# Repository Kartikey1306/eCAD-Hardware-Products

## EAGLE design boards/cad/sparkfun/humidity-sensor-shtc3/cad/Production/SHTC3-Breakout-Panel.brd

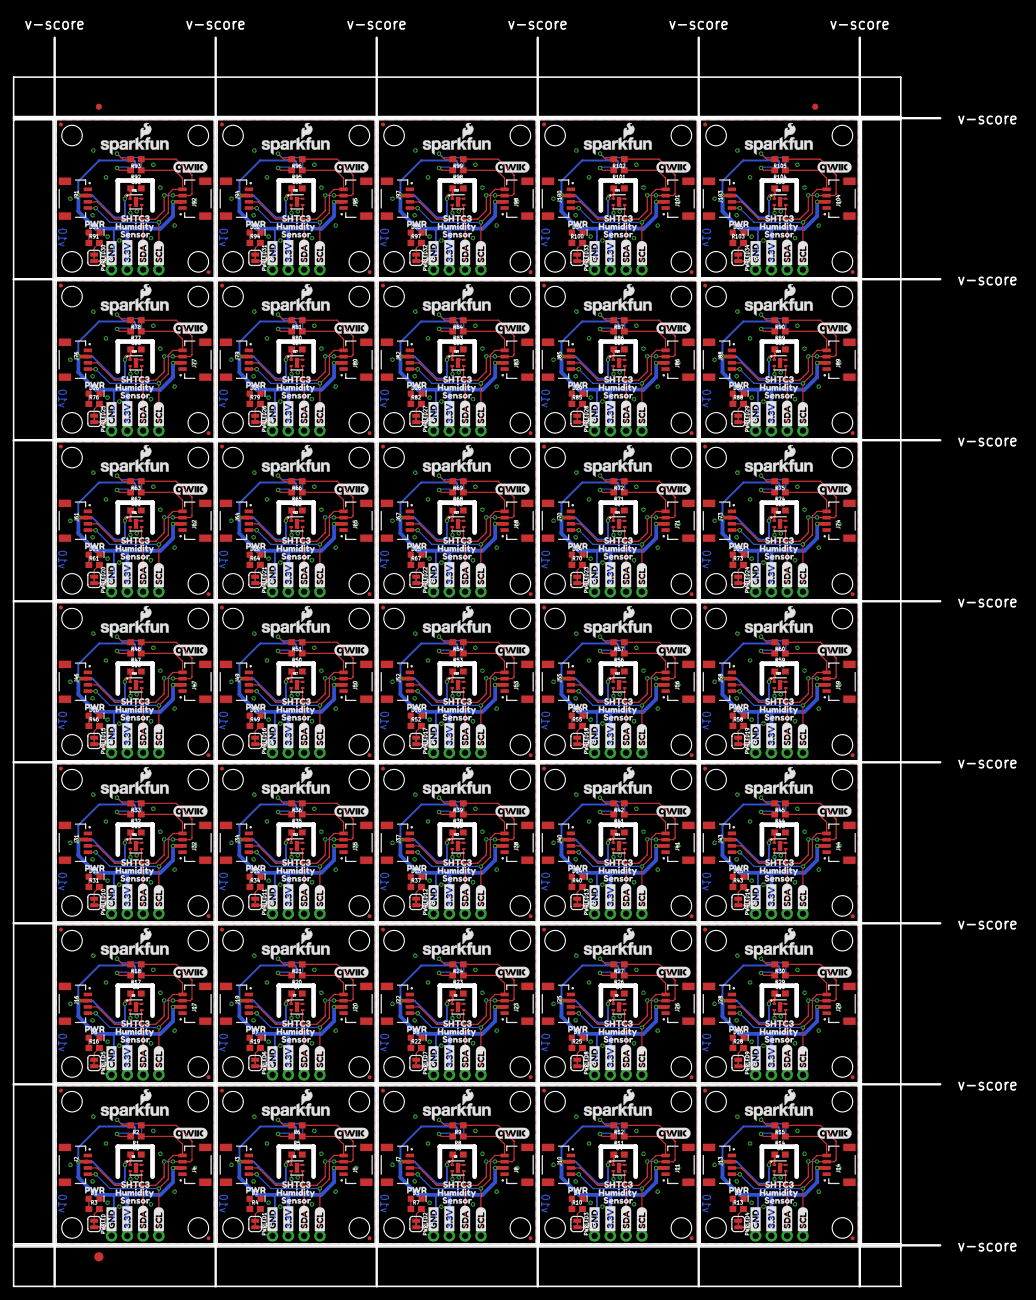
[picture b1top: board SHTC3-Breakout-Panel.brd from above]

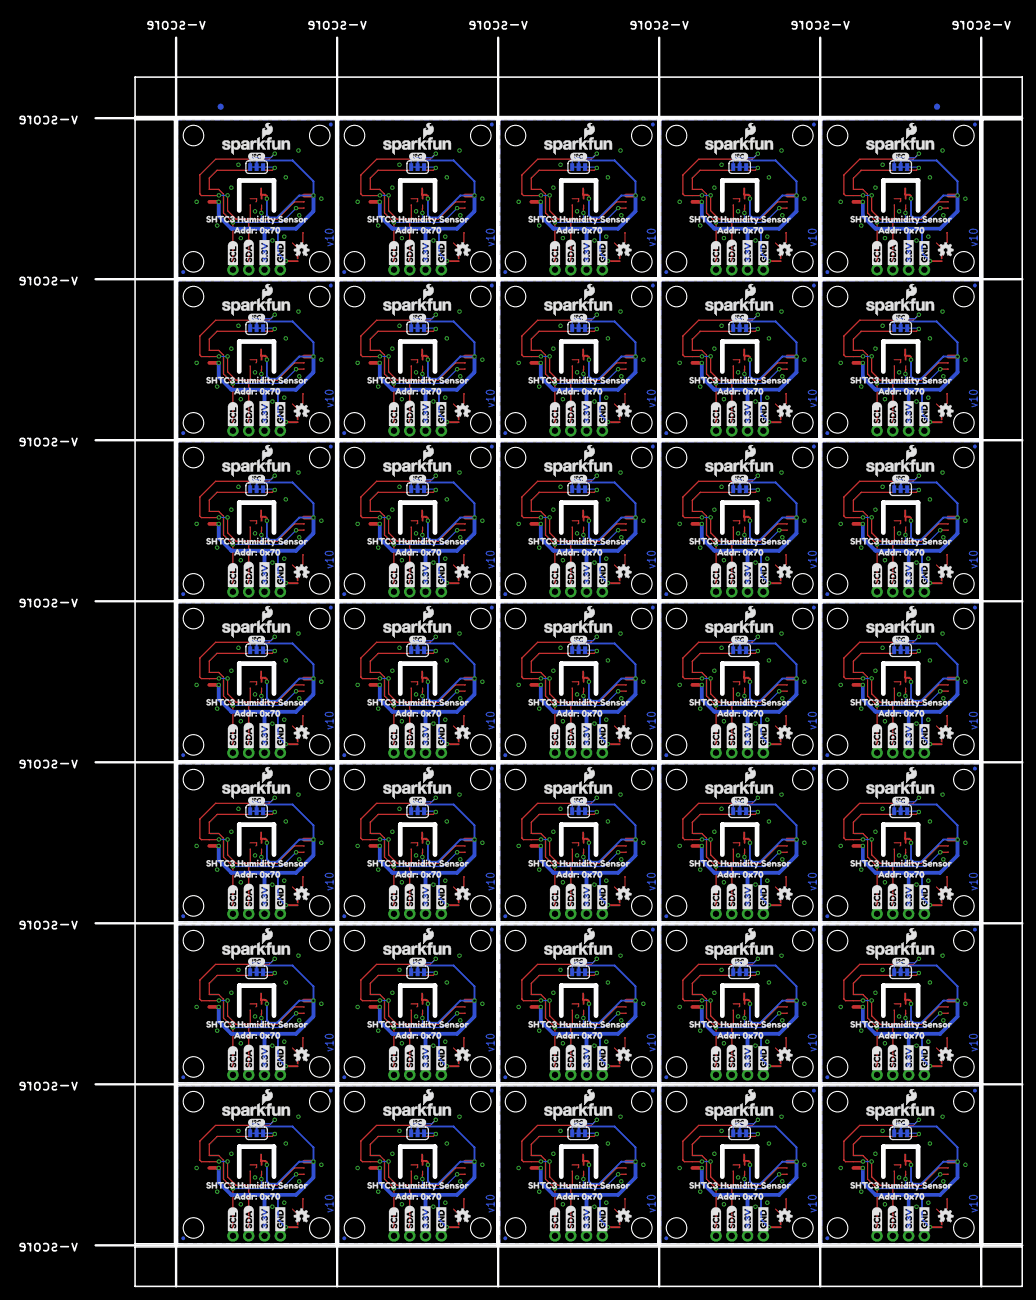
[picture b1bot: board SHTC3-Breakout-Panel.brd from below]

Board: 2 copper layers, 149.1 x 200.9 mm, 1370 parts (422 on the bottom side), 280 nets.

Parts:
C1, C2, C3, C4, C5, C6, C7, C8, C9, C10, C11, C12, C13, C14, C15, C16, C17, C18, C19, C20, C21, C22, C23, C24, C25, C26, C27, C28, C29, C30, C31, C32, C33, C34, C35: 0.1uF; 0603
D1, D2, D3, D4, D5, D6, D7, D8, D9, D10, D11, D12, D13, D14, D15, D16, D17, D18, D19, D20, D21, D22, D23, D24, D25, D26, D27, D28, D29, D30, D31, D32, D33, D34, D35: RED; LED-0603
E$1, E$2, E$3, E$4: FIDUCIAL-1X2
E$5: FIDUCIAL-1.5X3
I2C, I2C1, I2C2, I2C3, I2C4, I2C5, I2C6, I2C7, I2C8, I2C9, I2C10, I2C11, I2C12, I2C13, I2C14, I2C15, I2C16, I2C17, I2C18, I2C19, I2C20, I2C21, I2C22, I2C23, I2C24, I2C25, I2C26, I2C27, I2C28, I2C29, I2C30, I2C31, I2C32, I2C33, I2C34: JUMPER-SMT_3_2-NC_TRACE_SILK; SMT-JUMPER_3_2-NC_TRACE_SILK
J1, J6, J9, J12, J15, J18, J21, J24, J27, J30, J33, J36, J39, J42, J45, J48, J51, J54, J57, J60, J63, J66, J69, J72, J75, J78, J81, J84, J87, J90, J93, J96, J99, J102, J105: 1X04_NO_SILK
J2, J3, J4, J5, J7, J8, J10, J11, J13, J14, J16, J17, J19, J20, J22, J23, J25, J26, J28, J29, J31, J32, J34, J35, J37, J38, J40, J41, J43, J44, J46, J47, J49, J50, J52, J53, J55, J56, J58, J59, J61, J62, J64, J65, J67, J68, J70, J71, J73, J74, J76, J77, J79, J80, J82, J83, J85, J86, J88, J89, J91, J92, J94, J95, J97, J98, J100, J101, J103, J104: QWIIC_RIGHT_ANGLE; JST04_1MM_RA
JP1, JP2, JP5, JP6, JP11, JP12, JP13, JP14, JP19, JP20, JP21, JP22, JP27, JP28, JP29, JP30, JP35, JP36, JP37, JP38, JP43, JP44, JP45, JP46, JP51, JP52, JP53, JP54, JP59, JP60, JP61, JP62, JP67, JP68, JP69, JP70, JP75, JP76, JP77, JP78, JP83, JP84, JP85, JP86, JP91, JP92, JP93, JP94, JP99, JP100, JP101, JP102, JP107, JP108, JP109, JP110, JP115, JP116, JP117, JP118, JP123, JP124, JP125, JP126, JP131, JP132, JP133, JP134, JP139, JP140, JP141, JP142, JP147, JP148, JP149, JP150, JP155, JP156, JP157, JP158, JP163, JP164, JP165, JP166, JP171, JP172, JP173, JP174, JP179, JP180, JP181, JP182, JP187, JP188, JP189, JP190, JP195, JP196, JP197, JP198, JP203, JP204, JP205, JP206, JP211, JP212, JP213, JP214, JP219, JP220, JP221, JP222, JP227, JP228, JP229, JP230, JP235, JP236, JP237, JP238, JP243, JP244, JP245, JP246, JP251, JP252, JP253, JP254, JP259, JP260, JP261, JP262, JP267, JP268, JP269, JP270, JP275, JP276, JP277, JP278: FIDUCIALUFIDUCIAL; MICRO-FIDUCIAL
JP3, JP4, JP7, JP8, JP9, JP10, JP15, JP16, JP17, JP18, JP23, JP24, JP25, JP26, JP31, JP32, JP33, JP34, JP39, JP40, JP41, JP42, JP47, JP48, JP49, JP50, JP55, JP56, JP57, JP58, JP63, JP64, JP65, JP66, JP71, JP72, JP73, JP74, JP79, JP80, JP81, JP82, JP87, JP88, JP89, JP90, JP95, JP96, JP97, JP98, JP103, JP104, JP105, JP106, JP111, JP112, JP113, JP114, JP119, JP120, JP121, JP122, JP127, JP128, JP129, JP130, JP135, JP136, JP137, JP138, JP143, JP144, JP145, JP146, JP151, JP152, JP153, JP154, JP159, JP160, JP161, JP162, JP167, JP168, JP169, JP170, JP175, JP176, JP177, JP178, JP183, JP184, JP185, JP186, JP191, JP192, JP193, JP194, JP199, JP200, JP201, JP202, JP207, JP208, JP209, JP210, JP215, JP216, JP217, JP218, JP223, JP224, JP225, JP226, JP231, JP232, JP233, JP234, JP239, JP240, JP241, JP242, JP247, JP248, JP249, JP250, JP255, JP256, JP257, JP258, JP263, JP264, JP265, JP266, JP271, JP272, JP273, JP274, JP279, JP280: STAND-OFF
LOGO1, LOGO5, LOGO9, LOGO13, LOGO17, LOGO21, LOGO25, LOGO29, LOGO33, LOGO37, LOGO41, LOGO45, LOGO49, LOGO53, LOGO57, LOGO61, LOGO65, LOGO69, LOGO73, LOGO77, LOGO81, LOGO85, LOGO89, LOGO93, LOGO97, LOGO101, LOGO105, LOGO109, LOGO113, LOGO117, LOGO121, LOGO125, LOGO129, LOGO133, LOGO137: OSHW-LOGOMINI; OSHW-LOGO-MINI
LOGO2, LOGO3, LOGO6, LOGO7, LOGO10, LOGO11, LOGO14, LOGO15, LOGO18, LOGO19, LOGO22, LOGO23, LOGO26, LOGO27, LOGO30, LOGO31, LOGO34, LOGO35, LOGO38, LOGO39, LOGO42, LOGO43, LOGO46, LOGO47, LOGO50, LOGO51, LOGO54, LOGO55, LOGO58, LOGO59, LOGO62, LOGO63, LOGO66, LOGO67, LOGO70, LOGO71, LOGO74, LOGO75, LOGO78, LOGO79, LOGO82, LOGO83, LOGO86, LOGO87, LOGO90, LOGO91, LOGO94, LOGO95, LOGO98, LOGO99, LOGO102, LOGO103, LOGO106, LOGO107, LOGO110, LOGO111, LOGO114, LOGO115, LOGO118, LOGO119, LOGO122, LOGO123, LOGO126, LOGO127, LOGO130, LOGO131, LOGO134, LOGO135, LOGO138, LOGO139: SFE_LOGO_NAME_FLAME.1_INCH; SFE_LOGO_NAME_FLAME_.1
LOGO4, LOGO8, LOGO12, LOGO16, LOGO20, LOGO24, LOGO28, LOGO32, LOGO36, LOGO40, LOGO44, LOGO48, LOGO52, LOGO56, LOGO60, LOGO64, LOGO68, LOGO72, LOGO76, LOGO80, LOGO84, LOGO88, LOGO92, LOGO96, LOGO100, LOGO104, LOGO108, LOGO112, LOGO116, LOGO120, LOGO124, LOGO128, LOGO132, LOGO136, LOGO140: REVISION
PWRLED, PWRLED1, PWRLED2, PWRLED3, PWRLED4, PWRLED5, PWRLED6, PWRLED7, PWRLED8, PWRLED9, PWRLED10, PWRLED11, PWRLED12, PWRLED13, PWRLED14, PWRLED15, PWRLED16, PWRLED17, PWRLED18, PWRLED19, PWRLED20, PWRLED21, PWRLED22, PWRLED23, PWRLED24, PWRLED25, PWRLED26, PWRLED27, PWRLED28, PWRLED29, PWRLED30, PWRLED31, PWRLED32, PWRLED33, PWRLED34: JUMPER-SMT_2_NC_TRACE_SILK; SMT-JUMPER_2_NC_TRACE_SILK
R1, R2, R5, R6, R8, R9, R11, R12, R14, R15, R17, R18, R20, R21, R23, R24, R26, R27, R29, R30, R32, R33, R35, R36, R38, R39, R41, R42, R44, R45, R47, R48, R50, R51, R53, R54, R56, R57, R59, R60, R62, R63, R65, R66, R68, R69, R71, R72, R74, R75, R77, R78, R80, R81, R83, R84, R86, R87, R89, R90, R92, R93, R95, R96, R98, R99, R101, R102, R104, R105: 2.2k; 0603
R3, R4, R7, R10, R13, R16, R19, R22, R25, R28, R31, R34, R37, R40, R43, R46, R49, R52, R55, R58, R61, R64, R67, R70, R73, R76, R79, R82, R85, R88, R91, R94, R97, R100, R103: 1k; 0603
U1, U2, U3, U4, U5, U6, U7, U8, U9, U10, U11, U12, U13, U14, U15, U16, U17, U18, U19, U20, U21, U22, U23, U24, U25, U26, U27, U28, U29, U30, U31, U32, U33, U34, U35: SHTC3
U$1, U$25, U$43, U$59, U$75, U$91, U$107, U$123, U$139, U$155, U$171, U$187, U$203, U$219, U$235, U$251, U$267, U$283, U$299, U$315, U$331, U$347, U$363, U$379, U$395, U$411, U$427, U$443, U$459, U$475, U$491, U$507, U$523, U$539, U$555: ADDR#_0X700
U$2, U$28, U$44, U$60, U$76, U$92, U$108, U$124, U$140, U$156, U$172, U$188, U$204, U$220, U$236, U$252, U$268, U$284, U$300, U$316, U$332, U$348, U$364, U$380, U$396, U$412, U$428, U$444, U$460, U$476, U$492, U$508, U$524, U$540, U$556: PWR_TO
U$3, U$14, U$17, U$22, U$34, U$37, U$50, U$53, U$66, U$69, U$82, U$85, U$98, U$101, U$114, U$117, U$130, U$133, U$146, U$149, U$162, U$165, U$178, U$181, U$194, U$197, U$210, U$213, U$226, U$229, U$242, U$245, U$258, U$261, U$274, U$277, U$290, U$293, U$306, U$309, U$322, U$325, U$338, U$341, U$354, U$357, U$370, U$373, U$386, U$389, U$402, U$405, U$418, U$421, U$434, U$437, U$450, U$453, U$466, U$469, U$482, U$485, U$498, U$501, U$514, U$517, U$530, U$533, U$546, U$549: GND1
U$4, U$13, U$18, U$21, U$33, U$38, U$49, U$54, U$65, U$70, U$81, U$86, U$97, U$102, U$113, U$118, U$129, U$134, U$145, U$150, U$161, U$166, U$177, U$182, U$193, U$198, U$209, U$214, U$225, U$230, U$241, U$246, U$257, U$262, U$273, U$278, U$289, U$294, U$305, U$310, U$321, U$326, U$337, U$342, U$353, U$358, U$369, U$374, U$385, U$390, U$401, U$406, U$417, U$422, U$433, U$438, U$449, U$454, U$465, U$470, U$481, U$486, U$497, U$502, U$513, U$518, U$529, U$534, U$545, U$550: 3#3V2
U$5, U$16, U$19, U$27, U$36, U$39, U$52, U$55, U$68, U$71, U$84, U$87, U$100, U$103, U$116, U$119, U$132, U$135, U$148, U$151, U$164, U$167, U$180, U$183, U$196, U$199, U$212, U$215, U$228, U$231, U$244, U$247, U$260, U$263, U$276, U$279, U$292, U$295, U$308, U$311, U$324, U$327, U$340, U$343, U$356, U$359, U$372, U$375, U$388, U$391, U$404, U$407, U$420, U$423, U$436, U$439, U$452, U$455, U$468, U$471, U$484, U$487, U$500, U$503, U$516, U$519, U$532, U$535, U$548, U$551: SDA8
U$6, U$15, U$20, U$26, U$35, U$40, U$51, U$56, U$67, U$72, U$83, U$88, U$99, U$104, U$115, U$120, U$131, U$136, U$147, U$152, U$163, U$168, U$179, U$184, U$195, U$200, U$211, U$216, U$227, U$232, U$243, U$248, U$259, U$264, U$275, U$280, U$291, U$296, U$307, U$312, U$323, U$328, U$339, U$344, U$355, U$360, U$371, U$376, U$387, U$392, U$403, U$408, U$419, U$424, U$435, U$440, U$451, U$456, U$467, U$472, U$483, U$488, U$499, U$504, U$515, U$520, U$531, U$536, U$547, U$552: SCL9
U$7, U$32, U$48, U$64, U$80, U$96, U$112, U$128, U$144, U$160, U$176, U$192, U$208, U$224, U$240, U$256, U$272, U$288, U$304, U$320, U$336, U$352, U$368, U$384, U$400, U$416, U$432, U$448, U$464, U$480, U$496, U$512, U$528, U$544, U$560: SHTC3_HUMIDITY_SENSOR2
U$8, U$29, U$45, U$61, U$77, U$93, U$109, U$125, U$141, U$157, U$173, U$189, U$205, U$221, U$237, U$253, U$269, U$285, U$301, U$317, U$333, U$349, U$365, U$381, U$397, U$413, U$429, U$445, U$461, U$477, U$493, U$509, U$525, U$541, U$557: _SHTC31
U$9, U$23, U$41, U$57, U$73, U$89, U$105, U$121, U$137, U$153, U$169, U$185, U$201, U$217, U$233, U$249, U$265, U$281, U$297, U$313, U$329, U$345, U$361, U$377, U$393, U$409, U$425, U$441, U$457, U$473, U$489, U$505, U$521, U$537, U$553: I_SUPER2_C-()-03
U$10, U$30, U$46, U$62, U$78, U$94, U$110, U$126, U$142, U$158, U$174, U$190, U$206, U$222, U$238, U$254, U$270, U$286, U$302, U$318, U$334, U$350, U$366, U$382, U$398, U$414, U$430, U$446, U$462, U$478, U$494, U$510, U$526, U$542, U$558: HUMIDITY2
U$11, U$24, U$42, U$58, U$74, U$90, U$106, U$122, U$138, U$154, U$170, U$186, U$202, U$218, U$234, U$250, U$266, U$282, U$298, U$314, U$330, U$346, U$362, U$378, U$394, U$410, U$426, U$442, U$458, U$474, U$490, U$506, U$522, U$538, U$554: QWIIC_5.5MM
U$12, U$31, U$47, U$63, U$79, U$95, U$111, U$127, U$143, U$159, U$175, U$191, U$207, U$223, U$239, U$255, U$271, U$287, U$303, U$319, U$335, U$351, U$367, U$383, U$399, U$415, U$431, U$447, U$463, U$479, U$495, U$511, U$527, U$543, U$559: SENSOR0

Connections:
3.3V: C1.1, I2C.2, J1.2, J2.2, J4.2, PWRLED.2, U1.1
3.3V1: C2.1, I2C1.2, J3.2, J5.2, J6.2, PWRLED1.2, U2.1
3.3V2: C3.1, I2C2.2, J7.2, J8.2, J9.2, PWRLED2.2, U3.1
3.3V3: C4.1, I2C3.2, J10.2, J11.2, J12.2, PWRLED3.2, U4.1
3.3V4: C5.1, I2C4.2, J13.2, J14.2, J15.2, PWRLED4.2, U5.1
3.3V5: C6.1, I2C5.2, J16.2, J17.2, J18.2, PWRLED5.2, U6.1
3.3V6: C7.1, I2C6.2, J19.2, J20.2, J21.2, PWRLED6.2, U7.1
3.3V7: C8.1, I2C7.2, J22.2, J23.2, J24.2, PWRLED7.2, U8.1
3.3V8: C9.1, I2C8.2, J25.2, J26.2, J27.2, PWRLED8.2, U9.1
3.3V9: C10.1, I2C9.2, J28.2, J29.2, J30.2, PWRLED9.2, U10.1
3.3V10: C11.1, I2C10.2, J31.2, J32.2, J33.2, PWRLED10.2, U11.1
3.3V11: C12.1, I2C11.2, J34.2, J35.2, J36.2, PWRLED11.2, U12.1
3.3V12: C13.1, I2C12.2, J37.2, J38.2, J39.2, PWRLED12.2, U13.1
3.3V13: C14.1, I2C13.2, J40.2, J41.2, J42.2, PWRLED13.2, U14.1
3.3V14: C15.1, I2C14.2, J43.2, J44.2, J45.2, PWRLED14.2, U15.1
3.3V15: C16.1, I2C15.2, J46.2, J47.2, J48.2, PWRLED15.2, U16.1
3.3V16: C17.1, I2C16.2, J49.2, J50.2, J51.2, PWRLED16.2, U17.1
3.3V17: C18.1, I2C17.2, J52.2, J53.2, J54.2, PWRLED17.2, U18.1
3.3V18: C19.1, I2C18.2, J55.2, J56.2, J57.2, PWRLED18.2, U19.1
3.3V19: C20.1, I2C19.2, J58.2, J59.2, J60.2, PWRLED19.2, U20.1
3.3V20: C21.1, I2C20.2, J61.2, J62.2, J63.2, PWRLED20.2, U21.1
3.3V21: C22.1, I2C21.2, J64.2, J65.2, J66.2, PWRLED21.2, U22.1
3.3V22: C23.1, I2C22.2, J67.2, J68.2, J69.2, PWRLED22.2, U23.1
3.3V23: C24.1, I2C23.2, J70.2, J71.2, J72.2, PWRLED23.2, U24.1
3.3V24: C25.1, I2C24.2, J73.2, J74.2, J75.2, PWRLED24.2, U25.1
3.3V25: C26.1, I2C25.2, J76.2, J77.2, J78.2, PWRLED25.2, U26.1
3.3V26: C27.1, I2C26.2, J79.2, J80.2, J81.2, PWRLED26.2, U27.1
3.3V27: C28.1, I2C27.2, J82.2, J83.2, J84.2, PWRLED27.2, U28.1
3.3V28: C29.1, I2C28.2, J85.2, J86.2, J87.2, PWRLED28.2, U29.1
3.3V29: C30.1, I2C29.2, J88.2, J89.2, J90.2, PWRLED29.2, U30.1
3.3V30: C31.1, I2C30.2, J91.2, J92.2, J93.2, PWRLED30.2, U31.1
3.3V31: C32.1, I2C31.2, J94.2, J95.2, J96.2, PWRLED31.2, U32.1
3.3V32: C33.1, I2C32.2, J97.2, J98.2, J99.2, PWRLED32.2, U33.1
3.3V33: C34.1, I2C33.2, J100.2, J101.2, J102.2, PWRLED33.2, U34.1
3.3V34: C35.1, I2C34.2, J103.2, J104.2, J105.2, PWRLED34.2, U35.1
GND: C1.2, D1.C, J1.1, J2.1, J4.1, U1.4, U1.5
GND1: C2.2, D2.C, J3.1, J5.1, J6.1, U2.4, U2.5
GND2: C3.2, D3.C, J7.1, J8.1, J9.1, U3.4, U3.5
GND3: C4.2, D4.C, J10.1, J11.1, J12.1, U4.4, U4.5
GND4: C5.2, D5.C, J13.1, J14.1, J15.1, U5.4, U5.5
GND5: C6.2, D6.C, J16.1, J17.1, J18.1, U6.4, U6.5
GND6: C7.2, D7.C, J19.1, J20.1, J21.1, U7.4, U7.5
GND7: C8.2, D8.C, J22.1, J23.1, J24.1, U8.4, U8.5
GND8: C9.2, D9.C, J25.1, J26.1, J27.1, U9.4, U9.5
GND9: C10.2, D10.C, J28.1, J29.1, J30.1, U10.4, U10.5
GND10: C11.2, D11.C, J31.1, J32.1, J33.1, U11.4, U11.5
GND11: C12.2, D12.C, J34.1, J35.1, J36.1, U12.4, U12.5
GND12: C13.2, D13.C, J37.1, J38.1, J39.1, U13.4, U13.5
GND13: C14.2, D14.C, J40.1, J41.1, J42.1, U14.4, U14.5
GND14: C15.2, D15.C, J43.1, J44.1, J45.1, U15.4, U15.5
GND15: C16.2, D16.C, J46.1, J47.1, J48.1, U16.4, U16.5
GND16: C17.2, D17.C, J49.1, J50.1, J51.1, U17.4, U17.5
GND17: C18.2, D18.C, J52.1, J53.1, J54.1, U18.4, U18.5
GND18: C19.2, D19.C, J55.1, J56.1, J57.1, U19.4, U19.5
GND19: C20.2, D20.C, J58.1, J59.1, J60.1, U20.4, U20.5
GND20: C21.2, D21.C, J61.1, J62.1, J63.1, U21.4, U21.5
GND21: C22.2, D22.C, J64.1, J65.1, J66.1, U22.4, U22.5
GND22: C23.2, D23.C, J67.1, J68.1, J69.1, U23.4, U23.5
GND23: C24.2, D24.C, J70.1, J71.1, J72.1, U24.4, U24.5
GND24: C25.2, D25.C, J73.1, J74.1, J75.1, U25.4, U25.5
GND25: C26.2, D26.C, J76.1, J77.1, J78.1, U26.4, U26.5
GND26: C27.2, D27.C, J79.1, J80.1, J81.1, U27.4, U27.5
GND27: C28.2, D28.C, J82.1, J83.1, J84.1, U28.4, U28.5
GND28: C29.2, D29.C, J85.1, J86.1, J87.1, U29.4, U29.5
GND29: C30.2, D30.C, J88.1, J89.1, J90.1, U30.4, U30.5
GND30: C31.2, D31.C, J91.1, J92.1, J93.1, U31.4, U31.5
GND31: C32.2, D32.C, J94.1, J95.1, J96.1, U32.4, U32.5
GND32: C33.2, D33.C, J97.1, J98.1, J99.1, U33.4, U33.5
GND33: C34.2, D34.C, J100.1, J101.1, J102.1, U34.4, U34.5
GND34: C35.2, D35.C, J103.1, J104.1, J105.1, U35.4, U35.5
unnamed: I2C.3, R1.2
unnamed: I2C.1, R2.2
unnamed: D1.A, R3.1
unnamed: PWRLED.1, R3.2
unnamed: D2.A, R4.1
unnamed: I2C1.3, R5.2
unnamed: I2C1.1, R6.2
unnamed: PWRLED1.1, R4.2
unnamed: D3.A, R7.1
unnamed: I2C2.3, R8.2
unnamed: I2C2.1, R9.2
unnamed: PWRLED2.1, R7.2
unnamed: D4.A, R10.1
unnamed: I2C3.3, R11.2
unnamed: I2C3.1, R12.2
unnamed: PWRLED3.1, R10.2
unnamed: D5.A, R13.1
unnamed: I2C4.3, R14.2
unnamed: I2C4.1, R15.2
unnamed: PWRLED4.1, R13.2
unnamed: D6.A, R16.1
unnamed: I2C5.3, R17.2
unnamed: I2C5.1, R18.2
unnamed: PWRLED5.1, R16.2
unnamed: D7.A, R19.1
unnamed: I2C6.3, R20.2
unnamed: I2C6.1, R21.2
unnamed: PWRLED6.1, R19.2
unnamed: D8.A, R22.1
unnamed: I2C7.3, R23.2
unnamed: I2C7.1, R24.2
unnamed: PWRLED7.1, R22.2
unnamed: D9.A, R25.1
unnamed: I2C8.3, R26.2
unnamed: I2C8.1, R27.2
unnamed: PWRLED8.1, R25.2
unnamed: D10.A, R28.1
unnamed: I2C9.3, R29.2
unnamed: I2C9.1, R30.2
unnamed: PWRLED9.1, R28.2
unnamed: D11.A, R31.1
unnamed: I2C10.3, R32.2
unnamed: I2C10.1, R33.2
unnamed: PWRLED10.1, R31.2
unnamed: D12.A, R34.1
unnamed: I2C11.3, R35.2
unnamed: I2C11.1, R36.2
unnamed: PWRLED11.1, R34.2
unnamed: D13.A, R37.1
unnamed: I2C12.3, R38.2
unnamed: I2C12.1, R39.2
unnamed: PWRLED12.1, R37.2
unnamed: D14.A, R40.1
unnamed: I2C13.3, R41.2
unnamed: I2C13.1, R42.2
unnamed: PWRLED13.1, R40.2
unnamed: D15.A, R43.1
unnamed: I2C14.3, R44.2
unnamed: I2C14.1, R45.2
unnamed: PWRLED14.1, R43.2
unnamed: D16.A, R46.1
unnamed: I2C15.3, R47.2
unnamed: I2C15.1, R48.2
unnamed: PWRLED15.1, R46.2
unnamed: D17.A, R49.1
unnamed: I2C16.3, R50.2
unnamed: I2C16.1, R51.2
unnamed: PWRLED16.1, R49.2
unnamed: D18.A, R52.1
unnamed: I2C17.3, R53.2
unnamed: I2C17.1, R54.2
unnamed: PWRLED17.1, R52.2
unnamed: D19.A, R55.1
unnamed: I2C18.3, R56.2
unnamed: I2C18.1, R57.2
unnamed: PWRLED18.1, R55.2
unnamed: D20.A, R58.1
unnamed: I2C19.3, R59.2
unnamed: I2C19.1, R60.2
unnamed: PWRLED19.1, R58.2
unnamed: D21.A, R61.1
unnamed: I2C20.3, R62.2
unnamed: I2C20.1, R63.2
unnamed: PWRLED20.1, R61.2
unnamed: D22.A, R64.1
unnamed: I2C21.3, R65.2
unnamed: I2C21.1, R66.2
unnamed: PWRLED21.1, R64.2
unnamed: D23.A, R67.1
unnamed: I2C22.3, R68.2
unnamed: I2C22.1, R69.2
unnamed: PWRLED22.1, R67.2
unnamed: D24.A, R70.1
unnamed: I2C23.3, R71.2
unnamed: I2C23.1, R72.2
unnamed: PWRLED23.1, R70.2
unnamed: D25.A, R73.1
unnamed: I2C24.3, R74.2
unnamed: I2C24.1, R75.2
unnamed: PWRLED24.1, R73.2
unnamed: D26.A, R76.1
unnamed: I2C25.3, R77.2
unnamed: I2C25.1, R78.2
unnamed: PWRLED25.1, R76.2
unnamed: D27.A, R79.1
unnamed: I2C26.3, R80.2
unnamed: I2C26.1, R81.2
unnamed: PWRLED26.1, R79.2
unnamed: D28.A, R82.1
unnamed: I2C27.3, R83.2
unnamed: I2C27.1, R84.2
unnamed: PWRLED27.1, R82.2
unnamed: D29.A, R85.1
unnamed: I2C28.3, R86.2
unnamed: I2C28.1, R87.2
unnamed: PWRLED28.1, R85.2
unnamed: D30.A, R88.1
unnamed: I2C29.3, R89.2
unnamed: I2C29.1, R90.2
unnamed: PWRLED29.1, R88.2
unnamed: D31.A, R91.1
unnamed: I2C30.3, R92.2
unnamed: I2C30.1, R93.2
unnamed: PWRLED30.1, R91.2
unnamed: D32.A, R94.1
unnamed: I2C31.3, R95.2
unnamed: I2C31.1, R96.2
unnamed: PWRLED31.1, R94.2
unnamed: D33.A, R97.1
unnamed: I2C32.3, R98.2
unnamed: I2C32.1, R99.2
unnamed: PWRLED32.1, R97.2
unnamed: D34.A, R100.1
unnamed: I2C33.3, R101.2
unnamed: I2C33.1, R102.2
unnamed: PWRLED33.1, R100.2
unnamed: D35.A, R103.1
unnamed: I2C34.3, R104.2
unnamed: I2C34.1, R105.2
unnamed: PWRLED34.1, R103.2
SCL: J1.4, J2.4, J4.4, R1.1, U1.2
SCL1: J3.4, J5.4, J6.4, R5.1, U2.2
SCL2: J7.4, J8.4, J9.4, R8.1, U3.2
SCL3: J10.4, J11.4, J12.4, R11.1, U4.2
SCL4: J13.4, J14.4, J15.4, R14.1, U5.2
SCL5: J16.4, J17.4, J18.4, R17.1, U6.2
SCL6: J19.4, J20.4, J21.4, R20.1, U7.2
SCL7: J22.4, J23.4, J24.4, R23.1, U8.2
SCL8: J25.4, J26.4, J27.4, R26.1, U9.2
SCL9: J28.4, J29.4, J30.4, R29.1, U10.2
SCL10: J31.4, J32.4, J33.4, R32.1, U11.2
SCL11: J34.4, J35.4, J36.4, R35.1, U12.2
SCL12: J37.4, J38.4, J39.4, R38.1, U13.2
SCL13: J40.4, J41.4, J42.4, R41.1, U14.2
SCL14: J43.4, J44.4, J45.4, R44.1, U15.2
SCL15: J46.4, J47.4, J48.4, R47.1, U16.2
SCL16: J49.4, J50.4, J51.4, R50.1, U17.2
SCL17: J52.4, J53.4, J54.4, R53.1, U18.2
SCL18: J55.4, J56.4, J57.4, R56.1, U19.2
SCL19: J58.4, J59.4, J60.4, R59.1, U20.2
SCL20: J61.4, J62.4, J63.4, R62.1, U21.2
SCL21: J64.4, J65.4, J66.4, R65.1, U22.2
SCL22: J67.4, J68.4, J69.4, R68.1, U23.2
SCL23: J70.4, J71.4, J72.4, R71.1, U24.2
SCL24: J73.4, J74.4, J75.4, R74.1, U25.2
SCL25: J76.4, J77.4, J78.4, R77.1, U26.2
SCL26: J79.4, J80.4, J81.4, R80.1, U27.2
SCL27: J82.4, J83.4, J84.4, R83.1, U28.2
SCL28: J85.4, J86.4, J87.4, R86.1, U29.2
SCL29: J88.4, J89.4, J90.4, R89.1, U30.2
SCL30: J91.4, J92.4, J93.4, R92.1, U31.2
SCL31: J94.4, J95.4, J96.4, R95.1, U32.2
SCL32: J97.4, J98.4, J99.4, R98.1, U33.2
SCL33: J100.4, J101.4, J102.4, R101.1, U34.2
SCL34: J103.4, J104.4, J105.4, R104.1, U35.2
SDA: J1.3, J2.3, J4.3, R2.1, U1.3
SDA1: J3.3, J5.3, J6.3, R6.1, U2.3
SDA2: J7.3, J8.3, J9.3, R9.1, U3.3
SDA3: J10.3, J11.3, J12.3, R12.1, U4.3
SDA4: J13.3, J14.3, J15.3, R15.1, U5.3
SDA5: J16.3, J17.3, J18.3, R18.1, U6.3
SDA6: J19.3, J20.3, J21.3, R21.1, U7.3
SDA7: J22.3, J23.3, J24.3, R24.1, U8.3
SDA8: J25.3, J26.3, J27.3, R27.1, U9.3
SDA9: J28.3, J29.3, J30.3, R30.1, U10.3
SDA10: J31.3, J32.3, J33.3, R33.1, U11.3
SDA11: J34.3, J35.3, J36.3, R36.1, U12.3
SDA12: J37.3, J38.3, J39.3, R39.1, U13.3
SDA13: J40.3, J41.3, J42.3, R42.1, U14.3
SDA14: J43.3, J44.3, J45.3, R45.1, U15.3
SDA15: J46.3, J47.3, J48.3, R48.1, U16.3
SDA16: J49.3, J50.3, J51.3, R51.1, U17.3
SDA17: J52.3, J53.3, J54.3, R54.1, U18.3
SDA18: J55.3, J56.3, J57.3, R57.1, U19.3
SDA19: J58.3, J59.3, J60.3, R60.1, U20.3
SDA20: J61.3, J62.3, J63.3, R63.1, U21.3
SDA21: J64.3, J65.3, J66.3, R66.1, U22.3
SDA22: J67.3, J68.3, J69.3, R69.1, U23.3
SDA23: J70.3, J71.3, J72.3, R72.1, U24.3
SDA24: J73.3, J74.3, J75.3, R75.1, U25.3
SDA25: J76.3, J77.3, J78.3, R78.1, U26.3
SDA26: J79.3, J80.3, J81.3, R81.1, U27.3
SDA27: J82.3, J83.3, J84.3, R84.1, U28.3
SDA28: J85.3, J86.3, J87.3, R87.1, U29.3
SDA29: J88.3, J89.3, J90.3, R90.1, U30.3
SDA30: J91.3, J92.3, J93.3, R93.1, U31.3
SDA31: J94.3, J95.3, J96.3, R96.1, U32.3
SDA32: J97.3, J98.3, J99.3, R99.1, U33.3
SDA33: J100.3, J101.3, J102.3, R102.1, U34.3
SDA34: J103.3, J104.3, J105.3, R105.1, U35.3

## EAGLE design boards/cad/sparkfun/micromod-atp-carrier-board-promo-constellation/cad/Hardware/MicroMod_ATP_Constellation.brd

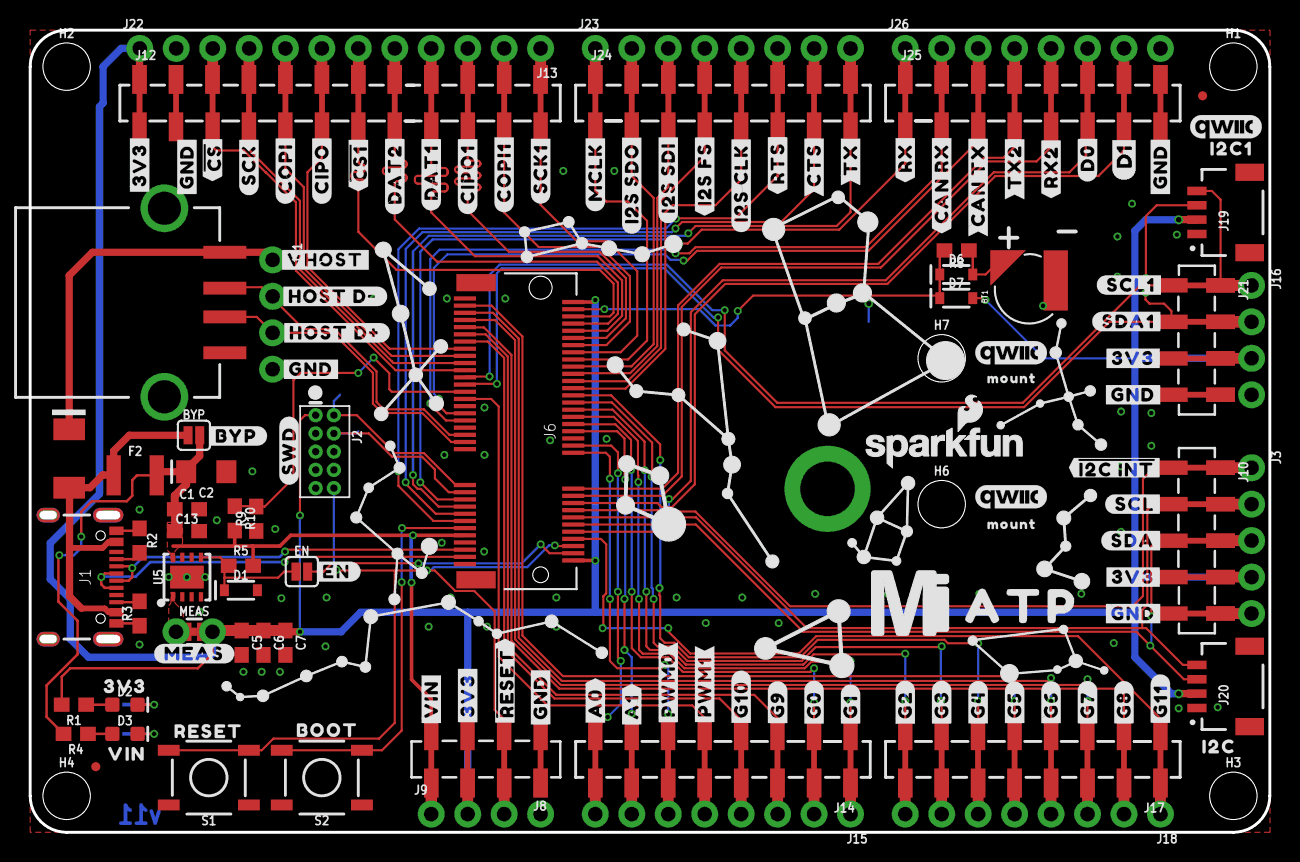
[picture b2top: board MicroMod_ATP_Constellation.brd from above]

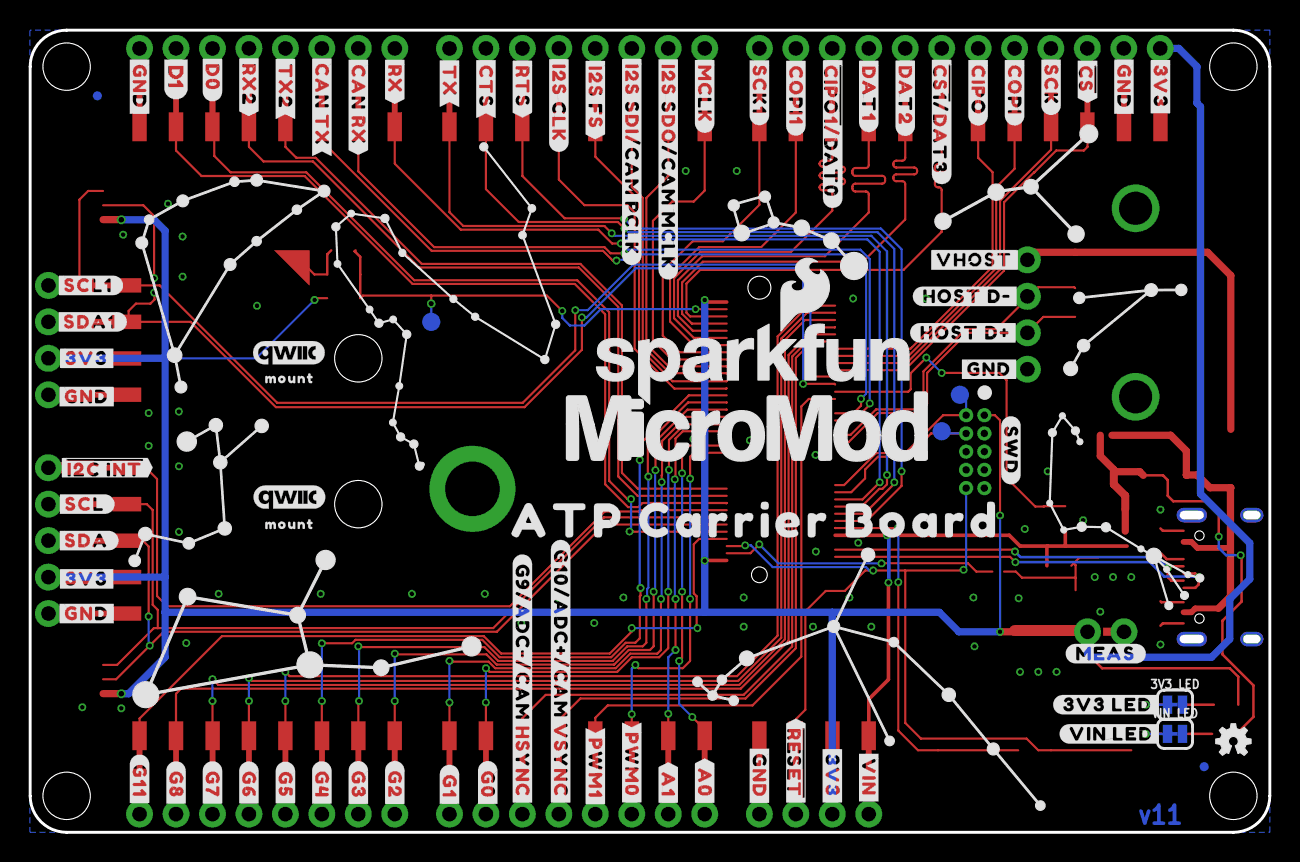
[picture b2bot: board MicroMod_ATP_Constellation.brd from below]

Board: 2 copper layers, 86.4 x 55.9 mm, 221 parts (80 on the bottom side), 71 nets.

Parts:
3V3_LED: JUMPER-SMT_2_NC_TRACE_SILK; SMT-JUMPER_2_NC_TRACE_SILK
BT1: ML414H; ML414H_IV01E
BYP: JUMPER-SMT_2_NO_SILK; SMT-JUMPER_2_NO_SILK
C1, C6: 0.1uF; 0603
C2: 10uF; EIA3216
C5: 1.0uF; 0603
C7, C13: 0.22uF; 0603
D1: 3.3V; SOD-323
D2, D3: RED; LED-0603
D4: 1A/15V/220mV; DO-214BA
D6: 3A/10V/280mV; SOD-323
D7: 1A/23V/620mV; SOD-323
EN: JUMPER-SMT_2_NO_SILK; SMT-JUMPER_2_NO_SILK
F2: 6V/2A; 1210
FD1, FD2, FD3, FD4: FIDUCIALUFIDUCIAL; FIDUCIAL-MICRO
FRAME1: FRAME-LEDGER; CREATIVE_COMMONS
H1, H2, H3, H4, H6, H7: STAND-OFF
H5: STAND-OFF-REFLOW2.5MM_TALL; STAND-OFF-REFLOW-M2.5
J1: USB-C-16P-2LAYER-PADS
J2: JTAG; 2X5-PTH-1.27MM
J3: 1X05_NO_SILK
J4: USB_A_SMT_FEMALE; USB-A-S-SILK-FEMALE
J6: MICROMOD-2222-C; M.2-CONNECTOR-E
J8, J21: 1X04_SMD_STRAIGHT_COMBO; 1X04_SMD_VERTICAL_COMBO
J9, J11, J16, J22: 1X04_NO_SILK
J10: 1X05_SMD_VERTICAL_COMBO
J12: 1X12_SMD_COMBINED
J13, J15, J18, J23, J26: 1X08_NO_SILK
J14, J17, J24, J25: 1X08_SMD_COMBINED
J19, J20: QWIIC_RIGHT_ANGLE; JST04_1MM_RA
LOGO1: SFE_LOGO_NAME_FLAME.1_INCH; SFE_LOGO_NAME_FLAME_.1
LOGO2: QWIIC_LOGO_5MM; QWIIC_5MM
LOGO3: OSHW-LOGOMINI; OSHW-LOGO-MINI
LOGO4: SFE_LOGO_NAME_FLAME.2_INCH; SFE_LOGO_NAME_FLAME_.2
LOGO5, LOGO6, LOGO7, LOGO8: QWIIC_LOGO_3MM; QWIIC_5MM
MEAS: COMBO-JUMPER_2_NC_TRACE
R1, R4, R8: 1k; 0603
R2, R3: 5.1k; 0603
R5: 100k; 0603
R9: 10k; 0603
R10: 20k; 0603
S1: Reset; TACTILE_SWITCH_SMD_5.2MM
S2: BOOT; TACTILE_SWITCH_SMD_5.2MM
TP1, TP2, TP3: TEST-POINT3X5; PAD.03X.05
U5: AP7361C-33; UDFN-8
U$1, U$123: #A0#10
U$2, U$124: #A1#10
U$3, U$27, U$46, U$47, U$58, U$89, U$100, U$101, U$102, U$103, U$104, U$105: #GND#0
U$4, U$120: #G0#2
U$5: #RESET10
U$6, U$98: #D0#0
U$7, U$119: #G1#2
U$8, U$118: #G2#2
U$9, U$117: #G3#3
U$10, U$116: #G4#4
U$11, U$115: #G5#5
U$12, U$114: #G6#6
U$13, U$113: #G7#7
U$14, U$112: #G8#8
U$15: #G9#9
U$16: #G10#10
U$17, U$111: #G11#10
U$18, U$121: #PWM0#10
U$19, U$122: #PWM1#10
U$20: ##CS1##5178039
U$21, U$110: ##I2C_INT##10
U$22: #CAN_RX#9
U$23, U$97: #CAN_TX#10
U$24: #CIPO#3
U$25: #COPI#2
U$26: #CTS#6
U$28: #SCK#2
U$29: #I2S_FS#5
U$30: #I2S_SDI#5
U$31: #I2S_SDO#5
U$32: #MCLK#4
U$33: #RTS#5
U$34: #RX#8
U$35: #TX#7
U$36: #DAT1#5178039
U$37, U$125: ##RESET##7
U$38, U$60, U$61, U$70, U$88, U$106, U$107, U$126: #3V3#1
U$39: #BYP#8
U$40, U$128: #HOST_D##9
U$41, U$129: #HOST_D##10
U$42, U$132: #MEAS#10
U$43: BOOT10
U$44, U$108: #SDA#4
U$45, U$127: #VIN#6
U$48: #EN#0
U$49, U$109: #SCL#5
U$50, U$146: #VHOST#0
U$51, U$131: #SWD#10
U$52: #I2S_CLK#5
U$53: #DAT2#5178039
U$54: #CIPO1#5178039
U$56: ##CIPO1##DAT0#5178038
U$57, U$75: #COPI1#2
U$59: ##CS##0
U$62: ATP0
U$63, U$76: #RX2#3
U$64, U$80: #TX2#2
U$65, U$78: #SCL1#3
U$66, U$79: #SDA1#3
U$67, U$77: #SCK1#2
U$68: VIN3
U$69: 3V34
U$71: I2C4
U$72: I2C14
U$73: ATP_CARRIER_BOARD1
U$81: ##CS##5178037
U$82: #DAT2#5
U$83: #DAT1#5
U$84: ##CS1##DAT3#5178037
U$85: #COPI#4
U$86: #SCK#4
U$87: #MCLK#6
U$90: #I2S_FS#7
U$91: #I2S_CLK#7
U$92: #RTS#7
U$93: #CTS#8
U$94: #TX#9
U$95: #RX#10
U$96: #CAN_RX#10
U$99, U$145: D10
U$133: #VIN_LED#10
U$134: #3V3_LED#10
U$135: #G9#ADC##CAM_HSYNC#9
U$136: #G10#ADC##CAM_VSYNC#10
U$137: #I2S_SDI#CAM_PCLK#7
U$138: #I2S_SDO#CAM_MCLK#7
U$139, U$141, U$142, U$143: MOUNT10
U$140: MICROMOD_MI_LOGO_1
U$144: MICROMOD_LOGO_1
U$147: #CIPO#5178038
VIN_LED: JUMPER-SMT_2_NC_TRACE_SILK; SMT-JUMPER_2_NC_TRACE_SILK

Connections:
3.3V: C5.1, C6.1, C7.1, D7.A, J2.1, J3.4, J6.2, J6.74, J8.3, J9.2, J10.4, J12.1, J16.3, J19.2, J20.2, J21.3, J22.1, MEAS.2, MEAS.4, R1.2
3.3V_EN: D1.C, EN.1, R5.1, U5.5
!BOOT!: J6.11, S2.3, S2.4
!CS1!/DAT3: J6.70, J12.7, J13.6
!CS!: J6.55, J12.3, J22.3
!RESET: J2.10, J6.6, J8.2, J9.3, S1.3, S1.4
A0: J6.34, J14.8, J15.8
A1: J6.38, J14.7, J15.7
CAN_RXI: J6.41, J25.2, J26.2
CAN_TXO: J6.43, J25.3, J26.3
CIPO: J6.61, J12.6, J13.7
CIPO1/DAT0: J6.64, J12.10, J13.3
COPI: J6.59, J12.5, J13.8
COPI1: J6.62, J12.11, J13.2
CTS1: J6.15, J23.7, J24.7
D0: J6.10, J25.6, J26.6
D1: J6.18, J25.7, J26.7
DAT1: J6.66, J12.9, J13.4
DAT2: J6.68, J12.8, J13.5
G0: J6.40, J14.2, J15.2
G1: J6.42, J14.1, J15.1
G2: J6.44, J17.8, J18.8
G3: J6.46, J17.7, J18.7
G4: J6.48, J17.6, J18.6
G5: J6.73, J17.5, J18.5
G6: J6.71, J17.4, J18.4
G7: J6.69, J17.3, J18.3
G8: J6.67, J17.2, J18.2
G9/ADC_N: J6.65, J14.3, J15.3
G10/ADC_P: J6.63, J14.4, J15.4
G11: J6.8, J17.1, J18.1
GND: 3V3_LED.2, BT1.-, C1.2, C2.-, C5.2, C6.2, C7.2, C13.2, D1.A, H5.1, J1.GND, J1.GND2, J2.3, J2.5, J2.9, J3.5, J4.GND, J4.SHLD1, J4.SHLD2, J6.1, J6.7, J6.33, J6.36, J6.39, J6.45, J6.75, J8.1, J9.4, J10.5, J11.4, J12.2, J16.4, J19.1, J20.1, J21.4, J22.2, J25.8, J26.8, R2.1, R3.1, R9.1, S1.1, S1.2, S2.1, S2.2, U5.4, U5.EP, VIN_LED.2
I2C_!INT: J3.1, J6.16, J10.1
I2S_CLK: J6.50, J23.5, J24.5
I2S_SDI: J6.54, J23.3, J24.3
I2S_SDO: J6.56, J23.2, J24.2
I2S_WS: J6.52, J23.4, J24.4
MCLK: J6.58, J23.1, J24.1
unnamed: D2.A, R1.1
unnamed: D3.A, R4.1
unnamed: 3V3_LED.1, D2.C
unnamed: D3.C, VIN_LED.1
unnamed: EN.2, J6.4
unnamed: D4.C, J4.VBUS, J11.1
unnamed: J1.A5, R2.2
unnamed: J1.B5, R3.2
unnamed: BT1.+, D6.A, R8.1
OUT_MEAS: MEAS.1, MEAS.3, U5.1
PWM0: J6.32, J14.6, J15.6
PWM1: J6.47, J14.5, J15.5
RTC_3V: D6.C, D7.C, J6.72, R8.2, TP1.P$1
RTS1: J6.13, J23.6, J24.6
RX1: J6.19, J25.1, J26.1
RX2: J6.20, J25.5, J26.5
SCK: J6.57, J12.4, J22.4
SCK1: J6.60, J12.12, J13.1
SCL: J3.2, J6.14, J10.2, J20.4
SCL1: J6.53, J16.1, J19.4, J21.1
SDA: J3.3, J6.12, J10.3, J20.3
SDA1: J6.51, J16.2, J19.3, J21.2
SWDCK: J2.4, J6.21, TP3.P$1
SWDIO: J2.2, J6.23, TP2.P$1
TX1: J6.17, J23.8, J24.8
TX2: J6.22, J25.4, J26.4
USBHOST_N: J4.D-, J6.37, J11.2
USBHOST_P: J4.D+, J6.35, J11.3
USB_N: J1.A7, J1.B7, J6.5
USB_P: J1.A6, J1.B6, J6.3
VIN: BYP.2, C1.1, C2.+, C13.1, F2.2, J6.9, J8.4, J9.1, R4.2, R5.2, R10.2, U5.8
VIN/3: J6.49, R9.2, R10.1
V_USB: BYP.1, D4.A, F2.1, J1.VBUS1, J1.VBUS2

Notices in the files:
parts and their libraries:
SparkFun-Resistors: Licensing: Creative Commons ShareAlike 4.0 International - https://creativecommons.org/licenses/by-sa/4.0
SparkFun-Aesthetics: Released under the Creative Commons Attribution Share-Alike 4.0 License
SparkFun-Aesthetics: https://creativecommons.org/licenses/by-sa/4.0
